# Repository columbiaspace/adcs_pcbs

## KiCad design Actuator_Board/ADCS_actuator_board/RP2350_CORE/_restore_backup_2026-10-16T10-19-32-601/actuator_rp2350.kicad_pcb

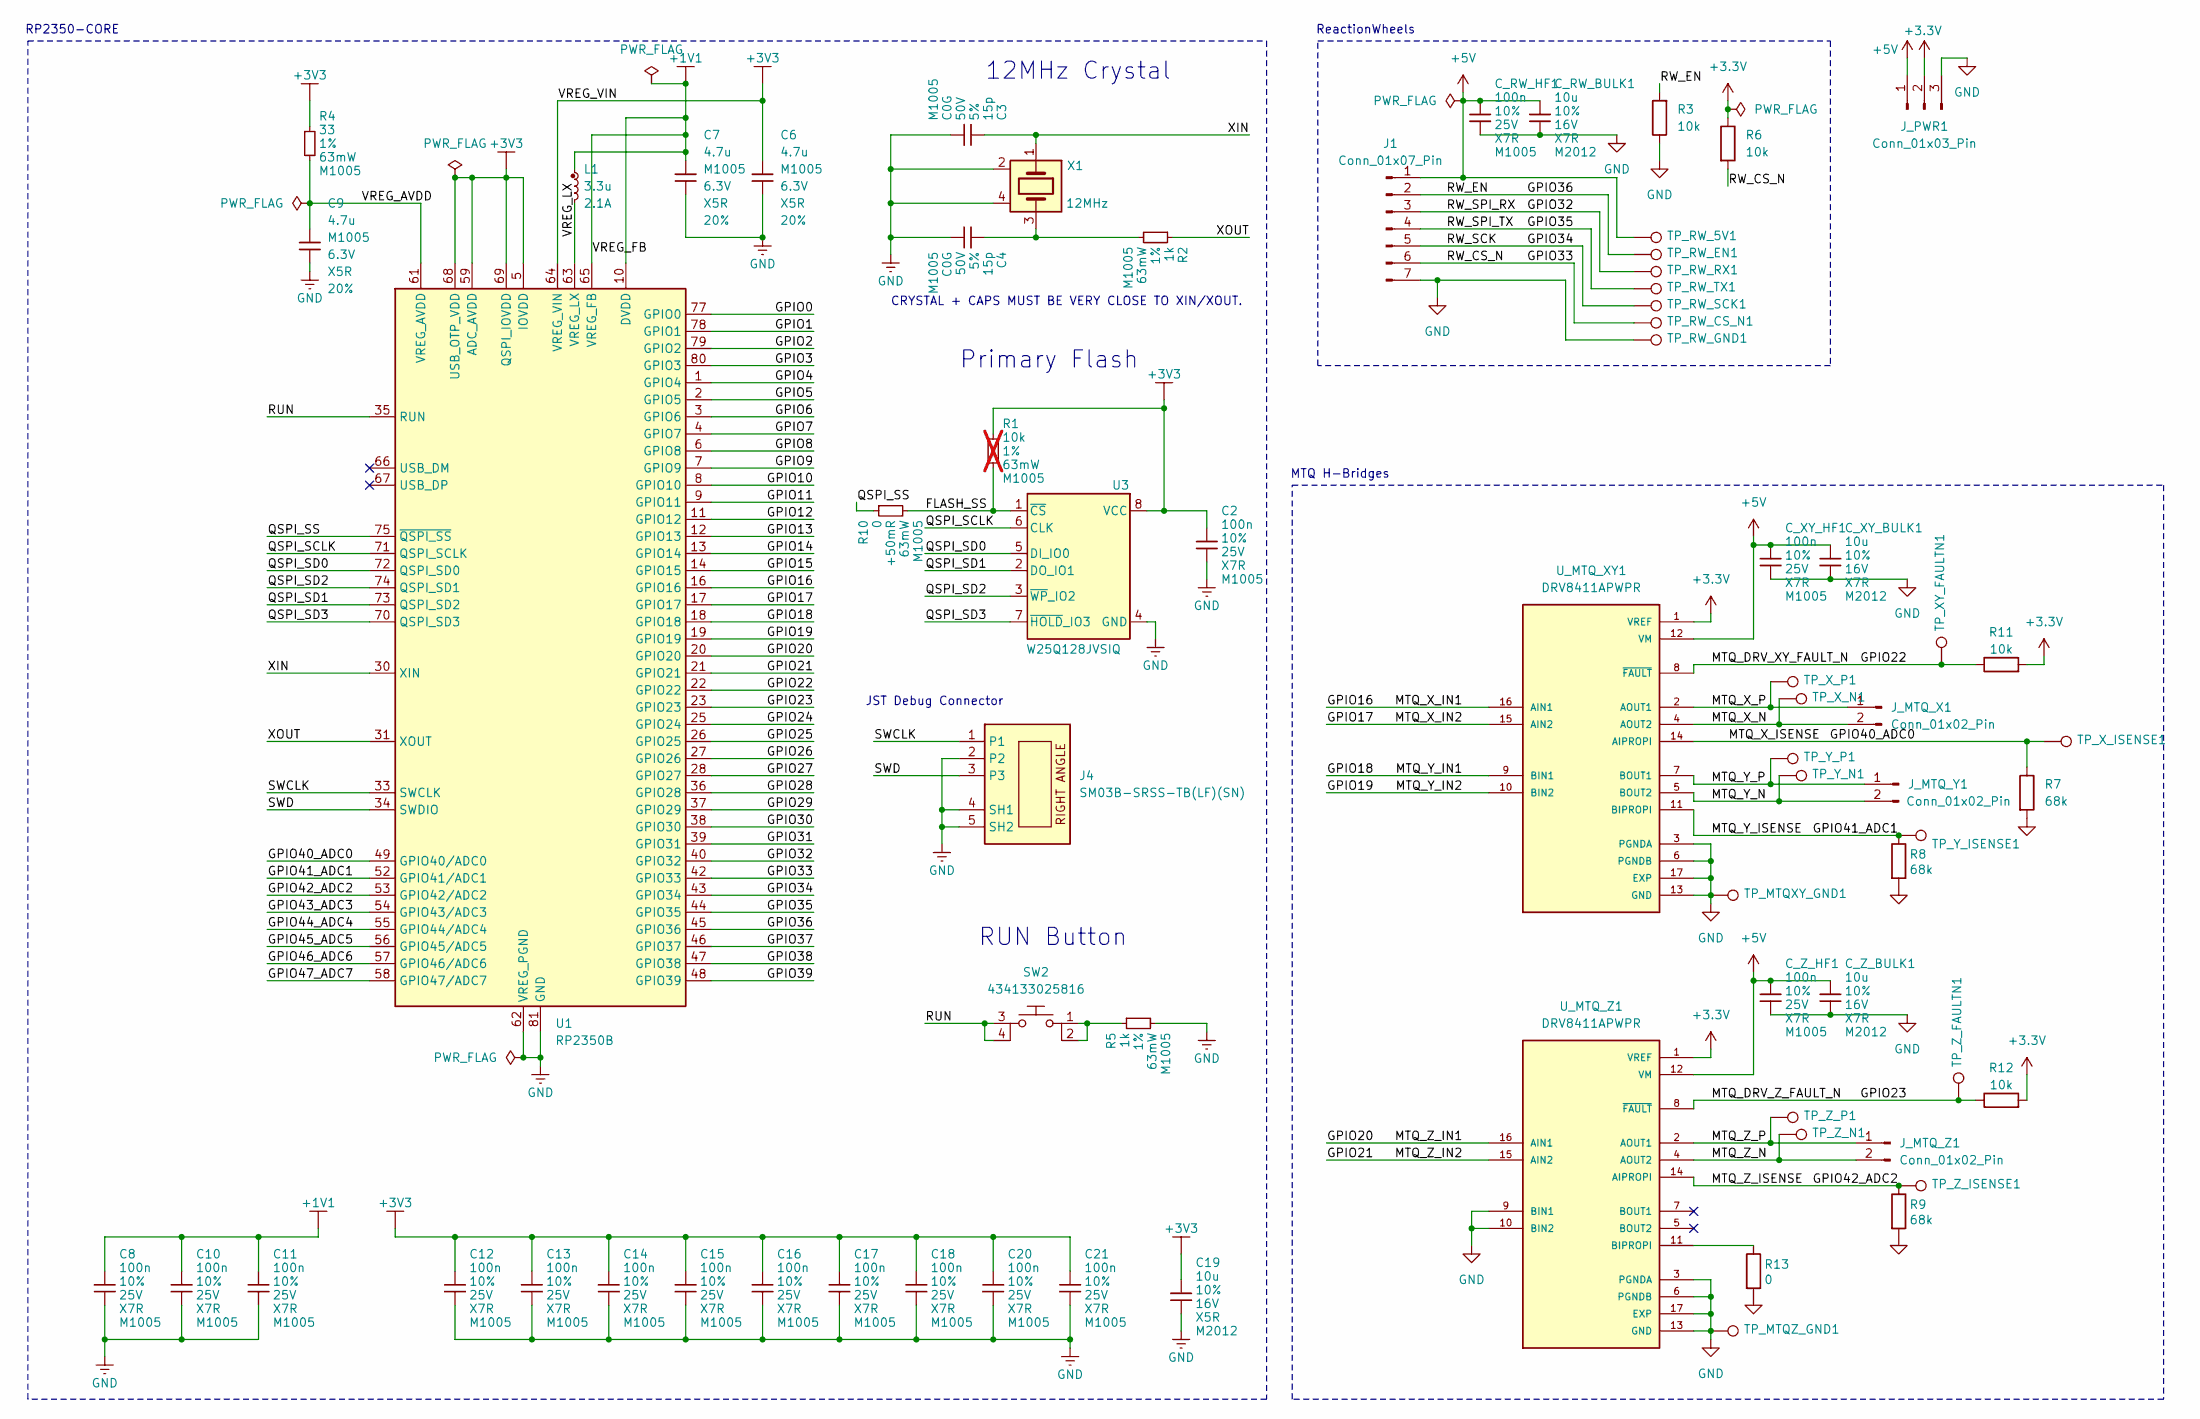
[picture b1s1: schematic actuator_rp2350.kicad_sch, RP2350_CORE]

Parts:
C2, C8, C10, C11, C12, C13, C14, C15, C16, C17, C18, C20, C21: 100n; generic_capc1005x50; voltage 25V; tolerance 10%; part_uid RP-01BJ9Y-KRGF41
C3, C4: 15p; generic_capc1005x50; voltage 50V; tolerance 5%; part_uid RP-01C89W-LLY9XV
C6, C7: 4.7u; generic_capc1005x50_wide; voltage 6.3V; tolerance 20%; part_uid RP-019A1P-0C2GHY
C9: 4.7u; generic_capc1005x50; voltage 6.3V; tolerance 20%; part_uid RP-019A1P-0C2GHY
C19: 10u; generic_capc2012x125; voltage 16V; tolerance 10%; part_uid RP-01GYSK-AVBE41
C_RW_BULK1: 10u; generic_capc2012x125; voltage 16V; tolerance 10%; part_uid RP-01GYSK-AVBE41
C_RW_HF1: 100n; generic_capc1005x50; voltage 25V; tolerance 10%; part_uid RP-01BJ9Y-KRGF41
C_XY_BULK1: 10u; generic_capc2012x125; voltage 16V; tolerance 10%; part_uid RP-01GYSK-AVBE41
C_XY_HF1: 100n; generic_capc1005x50; voltage 25V; tolerance 10%; part_uid RP-01BJ9Y-KRGF41
C_Z_BULK1: 10u; generic_capc2012x125; voltage 16V; tolerance 10%; part_uid RP-01GYSK-AVBE41
C_Z_HF1: 100n; generic_capc1005x50; voltage 25V; tolerance 10%; part_uid RP-01BJ9Y-KRGF41
J1: Conn_01x07_Pin
J4: SM03B-SRSS-TB(LF)(SN); jst_sm03b-srss-tb-lf--sn-; part_uid RP-01EKJ1-8V9SV1
J_MTQ_X1: Conn_01x02_Pin
J_MTQ_Y1: Conn_01x02_Pin
J_MTQ_Z1: Conn_01x02_Pin
J_PWR1: Conn_01x03_Pin
L1: 3.3u; abracon_aota-b201610s3r3-101-t; tolerance 20%; part_uid RP-01GY5D-2VC7WP
R1: 10k; generic_resc1005x35; tolerance 1%; voltage 50V; part_uid RP-019A1P-53DHSX; not fitted
R2, R5: 1k; generic_resc1005x35; tolerance 1%; voltage 50V; part_uid RP-019A1P-4Z6ZWY
R3, R6, R11, R12: 10k; generic_resc1005x35
R4: 33; generic_resc1005x35; tolerance 1%; voltage 50V; part_uid RP-019A1P-58PW9L
R7, R8, R9: 68k; generic_resc1005x35
R10: 0; generic_resc1005x35; tolerance +50mR; voltage 50V; part_uid RP-019A1P-4Y4V63
R13: 0; generic_resc1005x35
SW2: 434133025816; wurthelek_434133025816; part_uid RP-01H0MT-6E9H8F
TP_MTQXY_GND1: TestPoint; TestPoint_Pad_D1.0mm
TP_MTQZ_GND1: TestPoint; TestPoint_Pad_D1.0mm
TP_RW_5V1: TestPoint; TestPoint_Pad_D1.0mm
TP_RW_CS_N1: TestPoint; TestPoint_Pad_D1.0mm
TP_RW_EN1: TestPoint; TestPoint_Pad_D1.0mm
TP_RW_GND1: TestPoint; TestPoint_Pad_D1.0mm
TP_RW_RX1: TestPoint; TestPoint_Pad_D1.0mm
TP_RW_SCK1: TestPoint; TestPoint_Pad_D1.0mm
TP_RW_TX1: TestPoint; TestPoint_Pad_D1.0mm
TP_XY_FAULTN1: TestPoint; TestPoint_Pad_D1.0mm
TP_X_ISENSE1: TestPoint; TestPoint_Pad_D1.0mm
TP_X_N1: TestPoint; TestPoint_Pad_D1.0mm
TP_X_P1: TestPoint; TestPoint_Pad_D1.0mm
TP_Y_ISENSE1: TestPoint; TestPoint_Pad_D1.0mm
TP_Y_N1: TestPoint; TestPoint_Pad_D1.0mm
TP_Y_P1: TestPoint; TestPoint_Pad_D1.0mm
TP_Z_FAULTN1: TestPoint; TestPoint_Pad_D1.0mm
TP_Z_ISENSE1: TestPoint; TestPoint_Pad_D1.0mm
TP_Z_N1: TestPoint; TestPoint_Pad_D1.0mm
TP_Z_P1: TestPoint; TestPoint_Pad_D1.0mm
U1: RP2350B; QFN-80-1EP_10x10mm_P0.4mm_EP3.4x3.4mm
U3: W25Q128JVSIQ; generic_soic127p790x195-8; voltage 2.7-3.6V; part_uid RP-01JWD4-F1H4N9
U_MTQ_XY1: DRV8411APWPR; IC_DRV8411APWPR; PARTREV A
U_MTQ_Z1: DRV8411APWPR; IC_DRV8411APWPR; PARTREV A
X1: 12MHz; generic_xtalcc320x250x80-4; tolerance 30ppm; part_uid RP-01G8X7-GS352B

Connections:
+1V1: C7.1, C8.1, C10.1, C11.1, L1.1, U1.10 (DVDD), U1.32 (DVDD), U1.51 (DVDD), U1.65 (VREG_FB)
+3.3V: J_PWR1.2, R6.1, R11.2, R12.2, U_MTQ_XY1.1 (VREF), U_MTQ_Z1.1 (VREF)
+3V3: C2.1, C6.1, C12.1, C13.1, C14.1, C15.1, C16.1, C17.1, C18.1, C19.1, C20.1, C21.1, R1.1, R4.1, U1.5 (IOVDD), U1.15 (IOVDD), U1.24 (IOVDD), U1.29 (IOVDD), U1.41 (IOVDD), U1.50 (IOVDD), U1.59 (ADC_AVDD), U1.60 (IOVDD), U1.64 (VREG_VIN), U1.68 (USB_OTP_VDD), U1.69 (QSPI_IOVDD), U1.76 (IOVDD), U3.8 (VCC)
+5V: C_RW_BULK1.1, C_RW_HF1.1, C_XY_BULK1.1, C_XY_HF1.1, C_Z_BULK1.1, C_Z_HF1.1, J1.1, J_PWR1.1, TP_RW_5V1.1 (1_1), U_MTQ_XY1.12 (VM), U_MTQ_Z1.12 (VM)
/FLASH_SS: R1.2, R10.2, U3.1 (~CS)
/GPIO0: U1.77 (GPIO0)
/GPIO1: U1.78 (GPIO1)
/GPIO2: U1.79 (GPIO2)
/GPIO3: U1.80 (GPIO3)
/GPIO4: U1.1 (GPIO4)
/GPIO5: U1.2 (GPIO5)
/GPIO6: U1.3 (GPIO6)
/GPIO7: U1.4 (GPIO7)
/GPIO8: U1.6 (GPIO8)
/GPIO9: U1.7 (GPIO9)
/GPIO10: U1.8 (GPIO10)
/GPIO11: U1.9 (GPIO11)
/GPIO12: U1.11 (GPIO12)
/GPIO13: U1.12 (GPIO13)
/GPIO14: U1.13 (GPIO14)
/GPIO15: U1.14 (GPIO15)
/GPIO16: U1.16 (GPIO16), U_MTQ_XY1.16 (AIN1)
/GPIO17: U1.17 (GPIO17), U_MTQ_XY1.15 (AIN2)
/GPIO18: U1.18 (GPIO18), U_MTQ_XY1.9 (BIN1)
/GPIO19: U1.19 (GPIO19), U_MTQ_XY1.10 (BIN2)
/GPIO20: U1.20 (GPIO20), U_MTQ_Z1.16 (AIN1)
/GPIO21: U1.21 (GPIO21), U_MTQ_Z1.15 (AIN2)
/GPIO22: R11.1, TP_XY_FAULTN1.1 (1_1), U1.22 (GPIO22), U_MTQ_XY1.8 (~FAULT)
/GPIO23: R12.1, TP_Z_FAULTN1.1 (1_1), U1.23 (GPIO23), U_MTQ_Z1.8 (~FAULT)
/GPIO24: U1.25 (GPIO24)
/GPIO25: U1.26 (GPIO25)
/GPIO26: U1.27 (GPIO26)
/GPIO27: U1.28 (GPIO27)
/GPIO28: U1.36 (GPIO28)
/GPIO29: U1.37 (GPIO29)
/GPIO30: U1.38 (GPIO30)
/GPIO31: U1.39 (GPIO31)
/GPIO32: J1.3, TP_RW_RX1.1 (1_1), U1.40 (GPIO32)
/GPIO33: J1.6, R6.2, TP_RW_CS_N1.1 (1_1), U1.42 (GPIO33)
/GPIO34: J1.5, TP_RW_SCK1.1 (1_1), U1.43 (GPIO34)
/GPIO35: J1.4, TP_RW_TX1.1 (1_1), U1.44 (GPIO35)
/GPIO36: J1.2, R3.2, TP_RW_EN1.1 (1_1), U1.45 (GPIO36)
/GPIO37: U1.46 (GPIO37)
/GPIO38: U1.47 (GPIO38)
/GPIO39: U1.48 (GPIO39)
/GPIO40_ADC0: R7.1, TP_X_ISENSE1.1 (1_1), U1.49 (GPIO40/ADC0), U_MTQ_XY1.14 (AIPROPI)
/GPIO41_ADC1: R8.1, TP_Y_ISENSE1.1 (1_1), U1.52 (GPIO41/ADC1), U_MTQ_XY1.11 (BIPROPI)
/GPIO42_ADC2: R9.1, TP_Z_ISENSE1.1 (1_1), U1.53 (GPIO42/ADC2), U_MTQ_Z1.14 (AIPROPI)
/GPIO43_ADC3: U1.54 (GPIO43/ADC3)
/GPIO44_ADC4: U1.55 (GPIO44/ADC4)
/GPIO45_ADC5: U1.56 (GPIO45/ADC5)
/GPIO46_ADC6: U1.57 (GPIO46/ADC6)
/GPIO47_ADC7: U1.58 (GPIO47/ADC7)
/MTQ_X_N: J_MTQ_X1.2, TP_X_N1.1 (1_1), U_MTQ_XY1.4 (AOUT2)
/MTQ_X_P: J_MTQ_X1.1, TP_X_P1.1 (1_1), U_MTQ_XY1.2 (AOUT1)
/MTQ_Y_N: J_MTQ_Y1.2, TP_Y_N1.1 (1_1), U_MTQ_XY1.5 (BOUT2)
/MTQ_Y_P: J_MTQ_Y1.1, TP_Y_P1.1 (1_1), U_MTQ_XY1.7 (BOUT1)
/MTQ_Z_N: J_MTQ_Z1.2, TP_Z_N1.1 (1_1), U_MTQ_Z1.4 (AOUT2)
/MTQ_Z_P: J_MTQ_Z1.1, TP_Z_P1.1 (1_1), U_MTQ_Z1.2 (AOUT1)
/QSPI_SCLK: U1.71 (QSPI_SCLK), U3.6 (CLK)
/QSPI_SD0: U1.72 (QSPI_SD0), U3.5 (DI_IO0)
/QSPI_SD1: U1.73 (QSPI_SD2), U3.2 (DO_IO1)
/QSPI_SD2: U1.74 (QSPI_SD1), U3.3 (~WP_IO2)
/QSPI_SD3: U1.70 (QSPI_SD3), U3.7 (~HOLD_IO3)
/QSPI_SS: R10.1, U1.75 (~QSPI_SS)
/RUN: SW2.3, SW2.4, U1.35 (RUN)
/SWCLK: J4.1, U1.33 (SWCLK)
/SWD: J4.3, U1.34 (SWDIO)
/VREG_AVDD: C9.1, R4.2, U1.61 (VREG_AVDD)
/VREG_LX: L1.2, U1.63 (VREG_LX)
/XIN: C3.1, U1.30 (XIN), X1.1
/XOUT: R2.1, U1.31 (XOUT)
GND: C2.2, C3.2, C4.2, C6.2, C7.2, C8.2, C9.2, C10.2, C11.2, C12.2, C13.2, C14.2, C15.2, C16.2, C17.2, C18.2, C19.2, C20.2, C21.2, C_RW_BULK1.2, C_RW_HF1.2, C_XY_BULK1.2, C_XY_HF1.2, C_Z_BULK1.2, C_Z_HF1.2, J1.7, J4.2, J4.4 (SH1), J4.5 (SH2), J_PWR1.3, R3.1, R5.2, R7.2, R8.2, R9.2, R13.2, TP_MTQXY_GND1.1 (1_1), TP_MTQZ_GND1.1 (1_1), TP_RW_GND1.1 (1_1), U1.62 (VREG_PGND), U1.81 (GND), U3.4 (GND), U_MTQ_XY1.3 (PGNDA), U_MTQ_XY1.6 (PGNDB), U_MTQ_XY1.13 (GND), U_MTQ_XY1.17 (EXP), U_MTQ_Z1.3 (PGNDA), U_MTQ_Z1.6 (PGNDB), U_MTQ_Z1.9 (BIN1), U_MTQ_Z1.10 (BIN2), U_MTQ_Z1.13 (GND), U_MTQ_Z1.17 (EXP), X1.2, X1.4
unnamed: C4.1, R2.2, X1.3
unnamed: R5.1, SW2.1, SW2.2
unnamed: R13.1, U_MTQ_Z1.11 (BIPROPI)

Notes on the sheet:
JST Debug Connector
RP2350-CORE
ReactionWheels
MTQ H-Bridges
12MHz Crystal
Primary Flash
RUN Button
CRYSTAL + CAPS MUST BE VERY CLOSE TO XIN/XOUT.

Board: 4 copper layers, 64 parts (0 on the bottom side), 31 nets, no tracks yet.
